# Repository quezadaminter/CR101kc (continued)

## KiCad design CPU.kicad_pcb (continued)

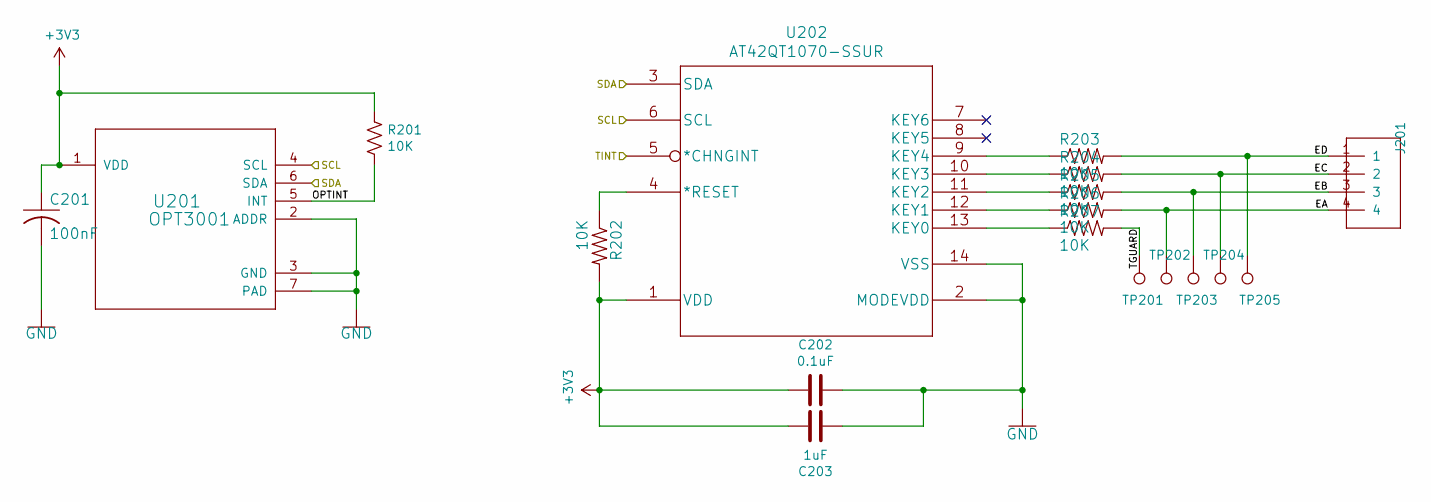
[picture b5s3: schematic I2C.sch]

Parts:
C201: 100nF; C_0805_2012Metric_Pad1.15x1.40mm_HandSolder; LCSC Part Number C49678
C202: 0.1uF; C_0805_2012Metric_Pad1.15x1.40mm_HandSolder; LCSC Part Number C49678
C203: 1uF; C_0805_2012Metric_Pad1.15x1.40mm_HandSolder; LCSC Part Number C28323
J201: 1X4SMD-FPC; KYOCERA-6227-FPC_FFC; DigiKey 046227004100829+
R201, R202, R203, R204, R205, R206, R207: 10K; R_0805_2012Metric_Pad1.15x1.40mm_HandSolder; LCSC Part Number C17414
TP201, TP202, TP203: TestPoint; TestPoint_Pad_D1.0mm
TP204: TestPoint; TestPoint_Pad_D1.0mm; DigiKey 709150001030006
TP205: TestPoint; TestPoint_Pad_D1.0mm; DigiKey ‎709150001040006
U201: OPT3001; DNP0006A; LCSC Part Number C90462
U202: AT42QT1070-SSUR; LCSC Part Number C461610

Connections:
+3V3: C201.1, C202.1, C203.2, R201.1, R202.2, U201.1 (VDD), U202.1 (VDD); also elsewhere on the board
/I2C Devices/EA: J201.4, R206.2, TP202.1
/I2C Devices/EB: J201.3, R205.2, TP203.1
/I2C Devices/EC: J201.2, R204.2, TP204.1
/I2C Devices/ED: J201.1, R203.2, TP205.1
/I2C Devices/OPTINT: R201.2, U201.5 (INT)
/I2C Devices/TGUARD: R207.2, TP201.1
/I2C Devices/TINT: U202.5 (*CHNGINT); also elsewhere on the board
/SCL: U201.4 (SCL), U202.6 (SCL); also elsewhere on the board
/SDA: U201.6 (SDA), U202.3 (SDA); also elsewhere on the board
GND: C201.2, C202.2, C203.1, U201.2 (ADDR), U201.3 (GND), U201.7 (PAD), U202.2 (MODEVDD), U202.14 (VSS); also elsewhere on the board
unnamed: R202.1, U202.4 (*RESET)
unnamed: R203.1, U202.9 (KEY4)
unnamed: R204.1, U202.10 (KEY3)
unnamed: R205.1, U202.11 (KEY2)
unnamed: R206.1, U202.12 (KEY1)
unnamed: R207.1, U202.13 (KEY0)

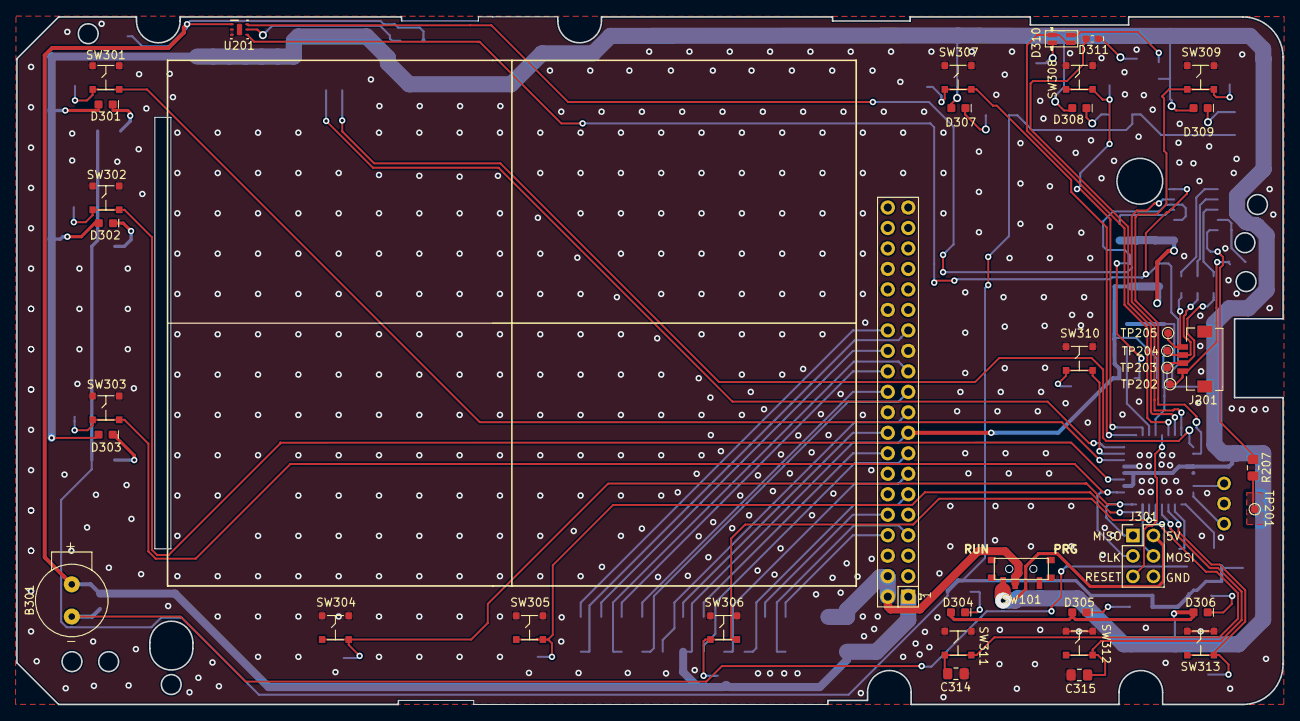
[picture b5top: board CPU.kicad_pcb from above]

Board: 2 copper layers, 157.0 x 85.3 mm, 90 parts (0 on the bottom side), 76 nets.

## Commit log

2020-04-12 Version 1.0 sent to fabrication 20200411.
2020-04-21 Last version before switching to resistive model to read the scroll wheel.
2020-04-23 Version 2, DRC and ERC clear, ready to send, waiting on V1 to see what did not work.
2020-04-23 Add gitignore.
2020-04-23 Moved CPU to separate directory in preparation for adding the power board project to the repository.
2020-04-23 Adding the power board project to the repository.
2020-04-23 Replacing old power board with PowerBoth.
2020-04-23 Added the remaining 3D models to the components. Not all are quite accurate but good for visualization. Credit for the RPiWZ 3D model goes to Kevin Schneider at https://gallery.autodesk.com/fusion360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
2020-05-01 Before correcting the PCB geometry.
2020-05-01 Fixed the PCB outlines so they are at the correct angles.
2020-05-03 Corrected the issues with v1 of the CPU board. Moved to 0.8mm board. Should be ready for another order.
2020-05-07 Rewiring the T84 to the 5 volt line.
2020-05-11 Moving signals to accomodate charger sensing.
2020-05-19 Updates from CPU v1 were completed. Switched out Tiny84 for a tiny1614 because the 84 lacks a hardware twi driver. This version was sent to production at jlcpcb.
2020-05-19 Cleanup to assemble the power board V2.
2020-05-19 Cleanup to assist the fabricator.
2020-05-22 Switch connector model. Reduce silk screen text size.
2020-05-22 Renaming components.
2020-05-26 Add display circuitry.
2020-06-01 Replacing the SEPIC converter.
2020-06-19 Move to separate branch to track CPU development separately.
2020-06-19 Separating the power board branch.
2020-06-24 Replacing the TFT. Before removing EEPROM and voltage monitor.
2020-06-24 BuyDisplay LCD.
2020-06-25 Move mounting holes on PCB closer to correct position.
2020-06-28 The layout is not optimal for the PB and two capacitor values for the buck are incorrect.
2020-06-29 Buck/boost v4.0.
2020-06-29 Sending v4.0 with new booster layout and fixed feedback resistors on buck converter.
2020-07-06 Update.
2020-07-17 Version 4 of the CPU board ordered with this commit.
2020-08-06 Fix placement of the RPi, prepare for V5.
2020-08-06 Should have been in previous commit.
2020-08-07 V5 Sent to fab.
2020-09-06 Moved LED up a bit. Increased buffer space around mounting hole to keep vias away from screw head. It's alive! With RPi and LCD on board. Still need to get scroll wheel to connect.
2021-01-18 Add files via upload
    Images of boards.
